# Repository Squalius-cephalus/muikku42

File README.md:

# Muikku42

Muikku42 is a Raspberry Pi Pico based 42-key column staggered split keyboard. The main goal is to make a affordable DIY split keyboard and keep the design simple. Easy of building is one of the main goal. Design is inpired from REVIUNG41 and Corne keyboards.

PCB is designed for MX style 5-pin switches, but with optional plate 3-pin switches can be used. PCB is reversible and same PCB design can be used as bottom plate.

***PCB design has not been tested. This is more of a concept than a real product. Current gerber-files should work just fine, but I still recommend checking for errors.***

QMK firmware is in the works.

## BOM - Bill of materials
|Part | Quantity |
|--|--|
| 5-pin MX compatible keyswitch | 42 |
| Kailh MX compatible hotswap socket | 42 |
| MX compatible 1u keycap | 42 |
| 2mm rubber feet | 16 |
| PCB | 2 |
| Raspberry Pi Pico | 2 |
| PJ320A Audio Socket | 2 |
| TRRS cable | 1 |
| USB-C cable | 1 |

If you are using 3-pin switches, 3D printed plate is required.

### TODO
1. Create firmware
2. Build guide

----
PCB design uses footprints from [ScottoKeebs](https://github.com/joe-scotto/scottokeebs/tree/main/Extras/ScottoKicad "ScottoKeebs"), [keyswitches.pretty](https://github.com/daprice/keyswitches.pretty "keyswitches.pretty")  and [kbd library.](https://github.com/foostan/kbd "kbd library.")

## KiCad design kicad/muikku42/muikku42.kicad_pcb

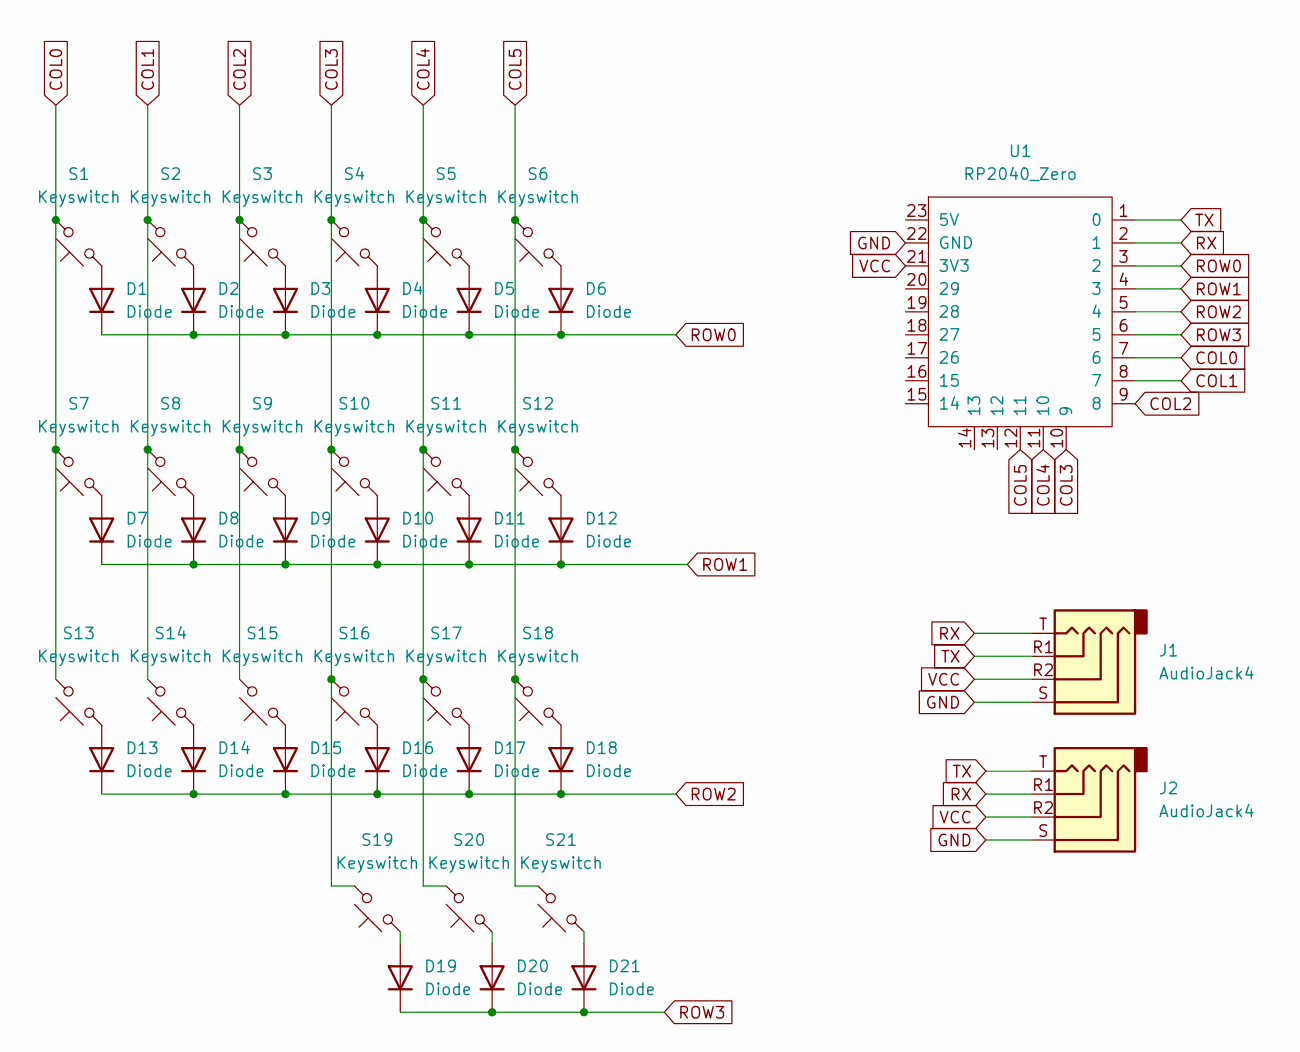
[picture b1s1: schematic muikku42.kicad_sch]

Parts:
D1, D2, D3, D4, D5, D6, D7, D8, D9, D10, D11, D12, D13, D14, D15, D16, D17, D18, D19, D20, D21: Diode; Diode_DO-35
J1, J2: AudioJack4; Jack_3.5mm_PJ320E_Horizontal
S1, S2, S3, S4, S5, S6, S7, S8, S9, S10, S11, S12, S13, S14, S15, S16, S17, S18, S19, S20, S21: Keyswitch; SW_MX_reversible
U1: RP2040_Zero

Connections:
COL0: S1.2, S7.2, S13.2, U1.7 (6)
COL1: S2.2, S8.2, S14.2, U1.8 (7)
COL2: S3.2, S9.2, S15.2, U1.9 (8)
COL3: S4.2, S10.2, S16.2, S19.2, U1.10 (9)
COL4: S5.2, S11.2, S17.2, S20.2, U1.11 (10)
COL5: S6.2, S12.2, S18.2, S21.2, U1.12 (11)
GND: J1.S, J2.S, U1.22 (GND)
unnamed: D1.2 (A), S1.1
unnamed: D2.2 (A), S2.1
unnamed: D3.2 (A), S3.1
unnamed: D4.2 (A), S4.1
unnamed: D5.2 (A), S5.1
unnamed: D6.2 (A), S6.1
unnamed: D7.2 (A), S7.1
unnamed: D8.2 (A), S8.1
unnamed: D9.2 (A), S9.1
unnamed: D10.2 (A), S10.1
unnamed: D11.2 (A), S11.1
unnamed: D12.2 (A), S12.1
unnamed: D13.2 (A), S13.1
unnamed: D14.2 (A), S14.1
unnamed: D15.2 (A), S15.1
unnamed: D16.2 (A), S16.1
unnamed: D17.2 (A), S17.1
unnamed: D18.2 (A), S18.1
unnamed: D19.2 (A), S19.1
unnamed: D20.2 (A), S20.1
unnamed: D21.2 (A), S21.1
ROW0: D1.1 (K), D2.1 (K), D3.1 (K), D4.1 (K), D5.1 (K), D6.1 (K), U1.3 (2)
ROW1: D7.1 (K), D8.1 (K), D9.1 (K), D10.1 (K), D11.1 (K), D12.1 (K), U1.4 (3)
ROW2: D13.1 (K), D14.1 (K), D15.1 (K), D16.1 (K), D17.1 (K), D18.1 (K), U1.5 (4)
ROW3: D19.1 (K), D20.1 (K), D21.1 (K), U1.6 (5)
RX: J1.T, J2.R1, U1.2 (1)
TX: J1.R1, J2.T, U1.1 (0)
VCC: J1.R2, J2.R2, U1.21 (3V3)

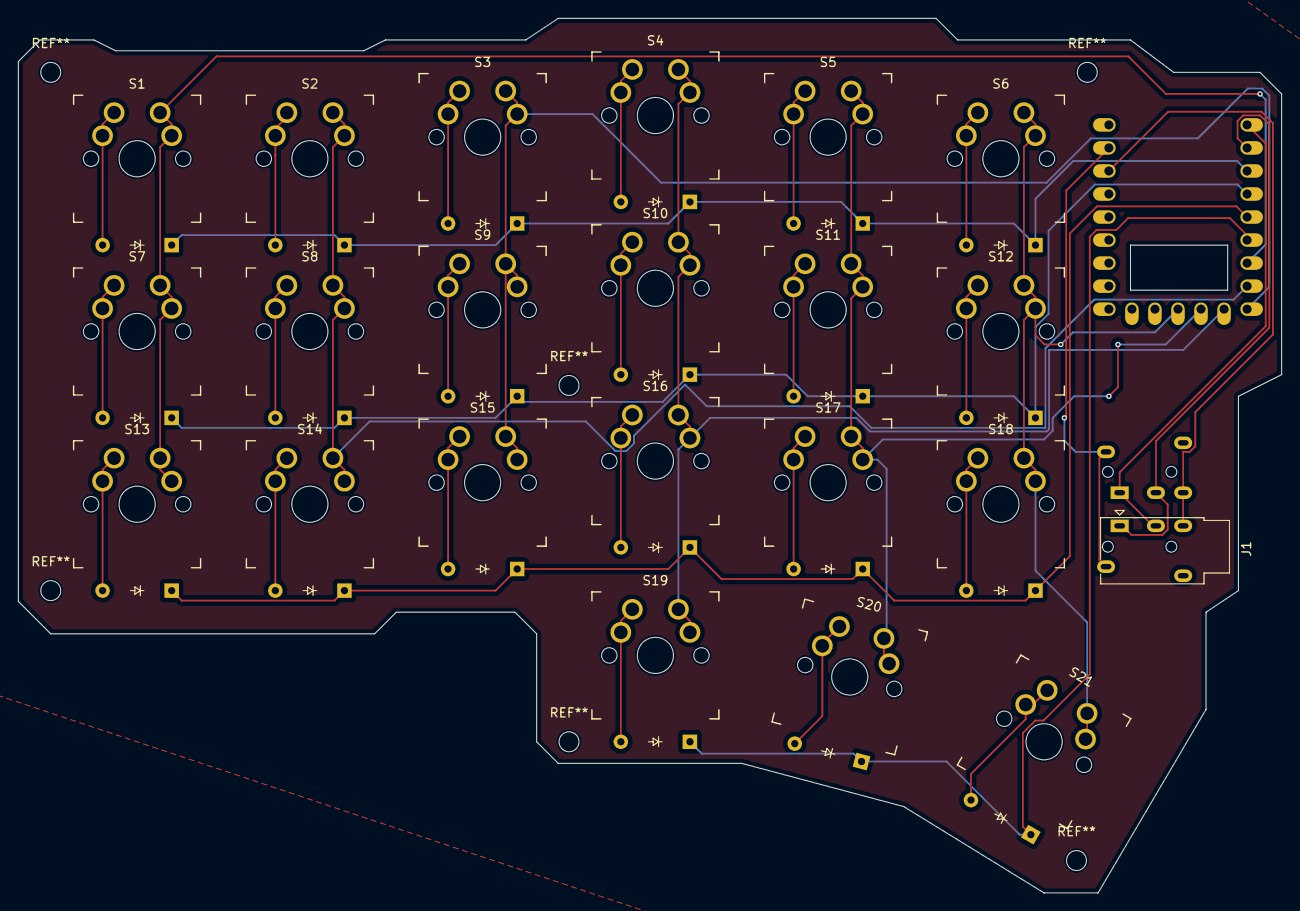
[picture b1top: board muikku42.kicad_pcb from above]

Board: 2 copper layers, 139.3 x 96.4 mm, 45 parts (1 on the bottom side), 35 nets.

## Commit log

2024-09-10 Added gerber files
2024-09-23 New PCB design and new info
    Everything has been updated, much simpler and cheaper design
2024-09-23 Fixed missing info
2024-09-23 Fixed image link
